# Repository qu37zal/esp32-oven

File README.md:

# esp32-oven
esp32-based temperature sensor/relay/wifi automation project to upcycle an inop "bradley" smoker

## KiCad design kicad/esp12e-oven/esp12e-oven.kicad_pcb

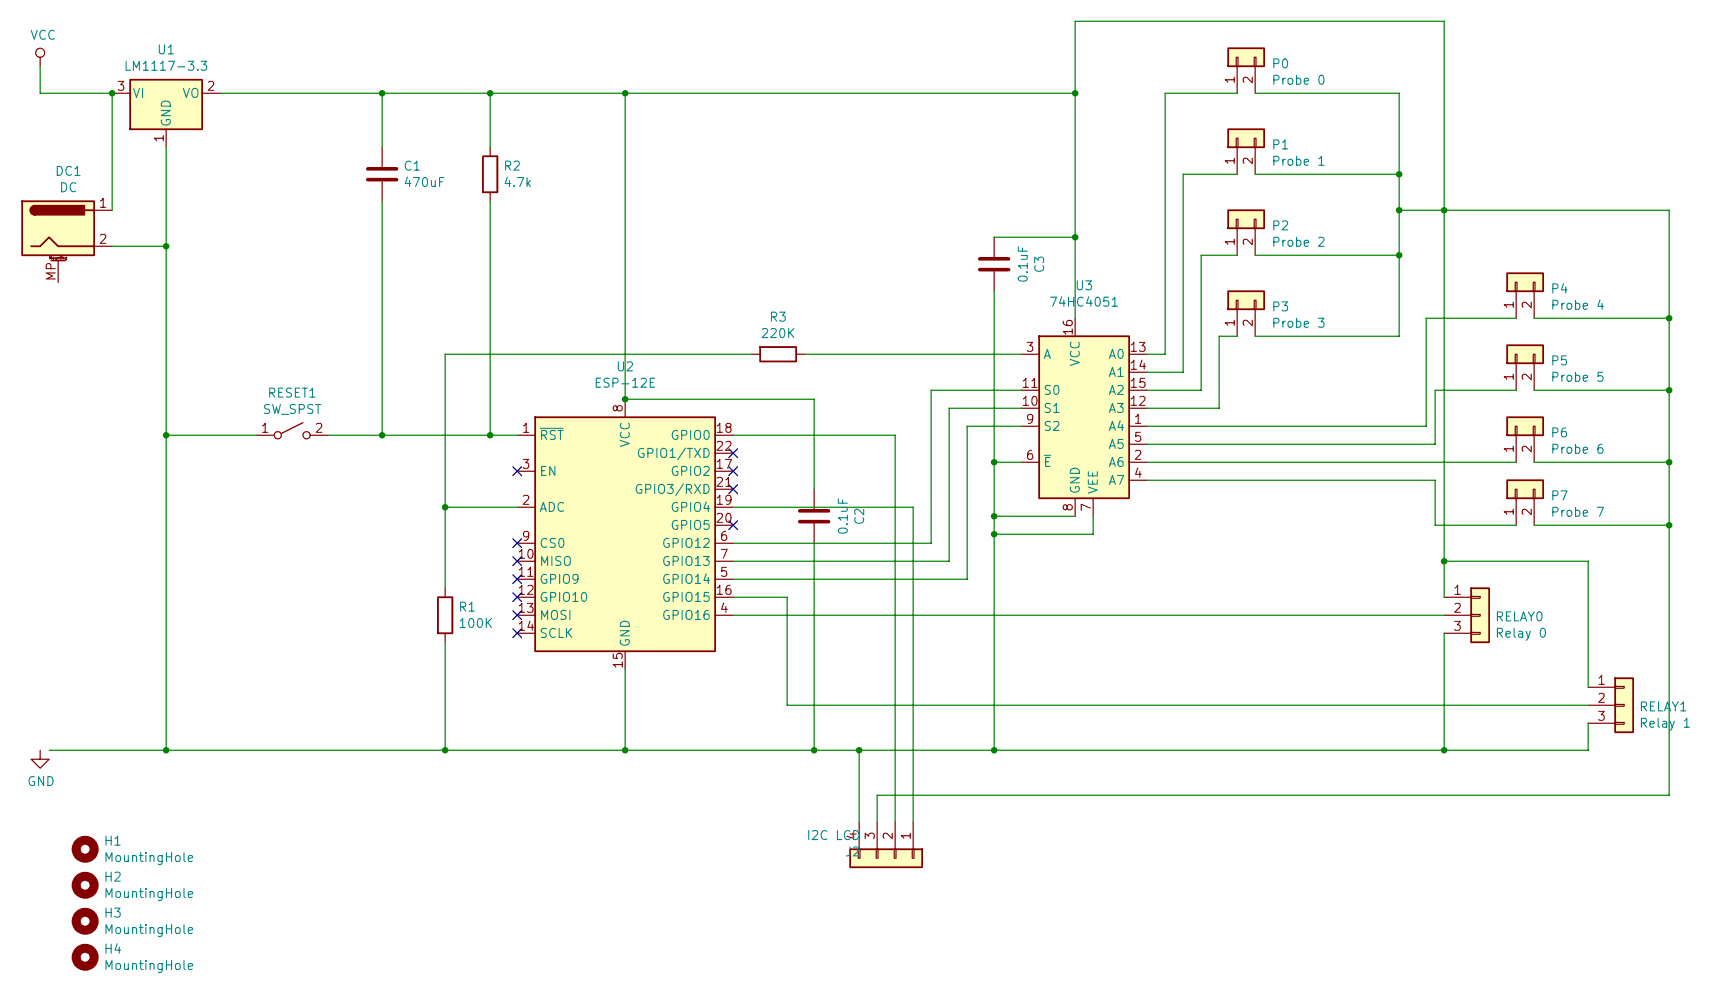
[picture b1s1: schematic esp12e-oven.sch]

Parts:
C1: 470uF; CP_Radial_D4.0mm_P1.50mm
C2, C3: 0.1uF; CP_Radial_D4.0mm_P1.50mm
DC1: DC; BarrelJack_Horizontal
H1, H2, H3, H4: MountingHole; MountingHole_2.5mm
J2: I2C LCD; PinHeader_1x04_P2.00mm_Vertical
P0: Probe 0; PinHeader_1x02_P2.00mm_Vertical
P1: Probe 1; PinHeader_1x02_P2.00mm_Vertical
P2: Probe 2; PinHeader_1x02_P2.00mm_Vertical
P3: Probe 3; PinHeader_1x02_P2.00mm_Vertical
P4: Probe 4; PinHeader_1x02_P2.00mm_Vertical
P5: Probe 5; PinHeader_1x02_P2.00mm_Vertical
P6: Probe 6; PinHeader_1x02_P2.00mm_Vertical
P7: Probe 7; PinHeader_1x02_P2.00mm_Vertical
R1: 100K; R_Axial_DIN0204_L3.6mm_D1.6mm_P5.08mm_Horizontal
R2: 4.7k; R_Axial_DIN0204_L3.6mm_D1.6mm_P5.08mm_Horizontal
R3: 220K; R_Axial_DIN0204_L3.6mm_D1.6mm_P5.08mm_Horizontal
RELAY0: Relay 0; PinSocket_1x03_P2.00mm_Horizontal
RELAY1: Relay 1; PinSocket_1x03_P2.00mm_Horizontal
RESET1: SW_SPST; KSA_Tactile_SPST
U1: LM1117-3.3; TO-220-3_Vertical
U2: ESP-12E
U3: 74HC4051; DIP-16_W7.62mm

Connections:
unnamed: C1.1, C2.2, C3.2, J2.3, P0.2, P1.2, P2.2, P3.2, P4.2, P5.2, P6.2, P7.2, R2.1, RELAY0.1, RELAY1.1, U1.2 (VO), U2.8 (VCC), U3.16 (VCC)
unnamed: C1.2, R2.2, RESET1.2 (B), U2.1 (~RST)
unnamed: C2.1, C3.1, DC1.2, J2.4, R1.2, RELAY0.3, RELAY1.3, RESET1.1 (A), U1.1 (GND), U2.15 (GND), U3.6 (~E), U3.7 (VEE), U3.8 (GND)
unnamed: J2.1, U2.19 (GPIO4)
unnamed: J2.2, U2.18 (GPIO0)
unnamed: P0.1, U3.13 (A0)
unnamed: P1.1, U3.14 (A1)
unnamed: P2.1, U3.15 (A2)
unnamed: P3.1, U3.12 (A3)
unnamed: P4.1, U3.1 (A4)
unnamed: P5.1, U3.5 (A5)
unnamed: P6.1, U3.2 (A6)
unnamed: P7.1, U3.4 (A7)
unnamed: R1.1, R3.2, U2.2 (ADC)
unnamed: R3.1, U3.3 (A)
unnamed: RELAY0.2, U2.4 (GPIO16)
unnamed: RELAY1.2, U2.16 (GPIO15)
unnamed: U2.5 (GPIO14), U3.9 (S2)
unnamed: U2.6 (GPIO12), U3.11 (S0)
unnamed: U2.7 (GPIO13), U3.10 (S1)
VCC: DC1.1, U1.3 (VI)

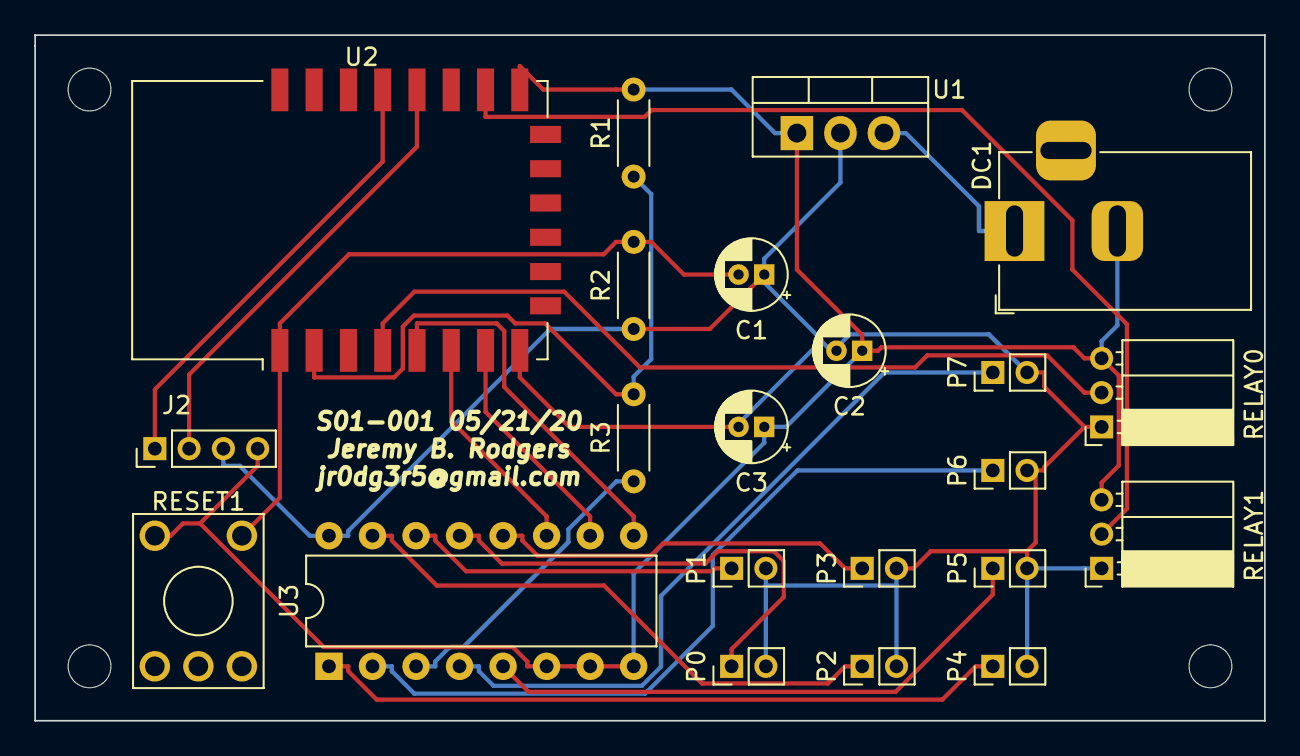
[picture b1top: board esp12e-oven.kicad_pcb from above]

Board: 2 copper layers, 71.8 x 40.0 mm, 26 parts (0 on the bottom side), 21 nets.

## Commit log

2020-05-20 Bump stringstream from 0.0.5 to 0.0.6 in /frontend
    Bumps [stringstream](https://github.com/mhart/StringStream) from 0.0.5 to 0.0.6.
    - [Release notes](https://github.com/mhart/StringStream/releases)
    - [Commits](https://github.com/mhart/StringStream/compare/v0.0.5...v0.0.6)
2020-05-20 Bump lodash.mergewith from 4.6.1 to 4.6.2 in /frontend
    Bumps [lodash.mergewith](https://github.com/lodash/lodash) from 4.6.1 to 4.6.2.
    - [Release notes](https://github.com/lodash/lodash/releases)
    - [Commits](https://github.com/lodash/lodash/commits)
2020-05-20 Bump js-yaml from 3.11.0 to 3.13.1 in /frontend
    Bumps [js-yaml](https://github.com/nodeca/js-yaml) from 3.11.0 to 3.13.1.
    - [Release notes](https://github.com/nodeca/js-yaml/releases)
    - [Changelog](https://github.com/nodeca/js-yaml/blob/master/CHANGELOG.md)
    - [Commits](https://github.com/nodeca/js-yaml/compare/3.11.0...3.13.1)
2020-05-20 Bump mixin-deep from 1.3.1 to 1.3.2 in /frontend
    Bumps [mixin-deep](https://github.com/jonschlinkert/mixin-deep) from 1.3.1 to 1.3.2.
    - [Release notes](https://github.com/jonschlinkert/mixin-deep/releases)
    - [Commits](https://github.com/jonschlinkert/mixin-deep/compare/1.3.1...1.3.2)
2020-05-20 added smoker arduino project
2020-05-20 added resource to maintain secrets (SSID etc)
2020-05-21 added kicad board layouts
2020-05-21 Revised boards
2020-05-21 moved arduino to firmware
2020-05-21 added backend and mongodb bindings
2020-05-21 added charting
2020-05-22 fixed async vue chart stuff
2020-05-22 graph updates
2020-05-26 some frontend work
2020-07-20 Bump lodash from 4.17.5 to 4.17.19 in /frontend
    Bumps [lodash](https://github.com/lodash/lodash) from 4.17.5 to 4.17.19.
    - [Release notes](https://github.com/lodash/lodash/releases)
    - [Commits](https://github.com/lodash/lodash/compare/4.17.5...4.17.19)
2020-07-20 Bump lodash from 4.17.15 to 4.17.19 in /backend
    Bumps [lodash](https://github.com/lodash/lodash) from 4.17.15 to 4.17.19.
    - [Release notes](https://github.com/lodash/lodash/releases)
    - [Commits](https://github.com/lodash/lodash/compare/4.17.15...4.17.19)
2020-09-03 Bump bl from 2.2.0 to 2.2.1 in /backend
    Bumps [bl](https://github.com/rvagg/bl) from 2.2.0 to 2.2.1.
    - [Release notes](https://github.com/rvagg/bl/releases)
    - [Commits](https://github.com/rvagg/bl/compare/v2.2.0...v2.2.1)
2020-12-04 Bump highlight.js from 9.15.9 to 9.18.5 in /frontend
    Bumps [highlight.js](https://github.com/highlightjs/highlight.js) from 9.15.9 to 9.18.5.
    - [Release notes](https://github.com/highlightjs/highlight.js/releases)
    - [Changelog](https://github.com/highlightjs/highlight.js/blob/9.18.5/CHANGES.md)
    - [Commits](https://github.com/highlightjs/highlight.js/compare/9.15.9...9.18.5)
2020-12-12 Bump ini from 1.3.5 to 1.3.8 in /frontend
    Bumps [ini](https://github.com/isaacs/ini) from 1.3.5 to 1.3.8.
    - [Release notes](https://github.com/isaacs/ini/releases)
    - [Commits](https://github.com/isaacs/ini/compare/v1.3.5...v1.3.8)
2020-12-12 Bump ini from 1.3.5 to 1.3.8 in /backend
    Bumps [ini](https://github.com/isaacs/ini) from 1.3.5 to 1.3.8.
    - [Release notes](https://github.com/isaacs/ini/releases)
    - [Commits](https://github.com/isaacs/ini/compare/v1.3.5...v1.3.8)
2021-01-06 Bump axios from 0.19.2 to 0.21.1 in /frontend
    Bumps [axios](https://github.com/axios/axios) from 0.19.2 to 0.21.1.
    - [Release notes](https://github.com/axios/axios/releases)
    - [Changelog](https://github.com/axios/axios/blob/v0.21.1/CHANGELOG.md)
    - [Commits](https://github.com/axios/axios/compare/v0.19.2...v0.21.1)
2021-03-10 Bump elliptic from 6.4.0 to 6.5.4 in /frontend
    Bumps [elliptic](https://github.com/indutny/elliptic) from 6.4.0 to 6.5.4.
    - [Release notes](https://github.com/indutny/elliptic/releases)
    - [Commits](https://github.com/indutny/elliptic/compare/v6.4.0...v6.5.4)
2021-03-31 Bump y18n from 3.2.1 to 3.2.2 in /backend
    Bumps [y18n](https://github.com/yargs/y18n) from 3.2.1 to 3.2.2.
    - [Release notes](https://github.com/yargs/y18n/releases)
    - [Changelog](https://github.com/yargs/y18n/blob/master/CHANGELOG.md)
    - [Commits](https://github.com/yargs/y18n/commits)
2021-04-01 Bump y18n from 3.2.1 to 3.2.2 in /frontend
    Bumps [y18n](https://github.com/yargs/y18n) from 3.2.1 to 3.2.2.
    - [Release notes](https://github.com/yargs/y18n/releases)
    - [Changelog](https://github.com/yargs/y18n/blob/master/CHANGELOG.md)
    - [Commits](https://github.com/yargs/y18n/commits)
2021-05-09 Bump url-parse from 1.4.7 to 1.5.1 in /frontend
    Bumps [url-parse](https://github.com/unshiftio/url-parse) from 1.4.7 to 1.5.1.
    - [Release notes](https://github.com/unshiftio/url-parse/releases)
    - [Commits](https://github.com/unshiftio/url-parse/compare/1.4.7...1.5.1)
2021-05-11 Bump lodash from 4.17.5 to 4.17.21 in /frontend
    Bumps [lodash](https://github.com/lodash/lodash) from 4.17.5 to 4.17.21.
    - [Release notes](https://github.com/lodash/lodash/releases)
    - [Commits](https://github.com/lodash/lodash/compare/4.17.5...4.17.21)
2021-05-11 Bump lodash from 4.17.15 to 4.17.21 in /backend
    Bumps [lodash](https://github.com/lodash/lodash) from 4.17.15 to 4.17.21.
    - [Release notes](https://github.com/lodash/lodash/releases)
    - [Commits](https://github.com/lodash/lodash/compare/4.17.15...4.17.21)
2021-05-11 Bump hosted-git-info from 2.6.0 to 2.8.9 in /frontend
    Bumps [hosted-git-info](https://github.com/npm/hosted-git-info) from 2.6.0 to 2.8.9.
    - [Release notes](https://github.com/npm/hosted-git-info/releases)
    - [Changelog](https://github.com/npm/hosted-git-info/blob/v2.8.9/CHANGELOG.md)
    - [Commits](https://github.com/npm/hosted-git-info/compare/v2.6.0...v2.8.9)
2021-05-26 Bump browserslist from 4.6.6 to 4.16.6 in /frontend
    Bumps [browserslist](https://github.com/browserslist/browserslist) from 4.6.6 to 4.16.6.
    - [Release notes](https://github.com/browserslist/browserslist/releases)
    - [Changelog](https://github.com/browserslist/browserslist/blob/main/CHANGELOG.md)
    - [Commits](https://github.com/browserslist/browserslist/compare/4.6.6...4.16.6)
2021-05-28 Bump dns-packet from 1.3.1 to 1.3.4 in /frontend
    Bumps [dns-packet](https://github.com/mafintosh/dns-packet) from 1.3.1 to 1.3.4.
    - [Release notes](https://github.com/mafintosh/dns-packet/releases)
    - [Changelog](https://github.com/mafintosh/dns-packet/blob/master/CHANGELOG.md)
    - [Commits](https://github.com/mafintosh/dns-packet/compare/v1.3.1...v1.3.4)
2021-08-04 Bump tar from 2.2.1 to 2.2.2 in /frontend
    Bumps [tar](https://github.com/npm/node-tar) from 2.2.1 to 2.2.2.
    - [Release notes](https://github.com/npm/node-tar/releases)
    - [Changelog](https://github.com/npm/node-tar/blob/main/CHANGELOG.md)
    - [Commits](https://github.com/npm/node-tar/compare/v2.2.1...v2.2.2)
    ---
    updated-dependencies:
2021-08-12 Bump path-parse from 1.0.5 to 1.0.7 in /frontend
    Bumps [path-parse](https://github.com/jbgutierrez/path-parse) from 1.0.5 to 1.0.7.
    - [Release notes](https://github.com/jbgutierrez/path-parse/releases)
    - [Commits](https://github.com/jbgutierrez/path-parse/commits/v1.0.7)
    ---
    updated-dependencies:
    - dependency-name: path-parse
2021-10-06 Bump url-parse from 1.4.7 to 1.5.3 in /frontend
    Bumps [url-parse](https://github.com/unshiftio/url-parse) from 1.4.7 to 1.5.3.
    - [Release notes](https://github.com/unshiftio/url-parse/releases)
    - [Commits](https://github.com/unshiftio/url-parse/compare/1.4.7...1.5.3)
    ---
    updated-dependencies:
    - dependency-name: url-parse
2022-02-19 Bump url-parse from 1.4.7 to 1.5.7 in /frontend
    Bumps [url-parse](https://github.com/unshiftio/url-parse) from 1.4.7 to 1.5.7.
    - [Release notes](https://github.com/unshiftio/url-parse/releases)
    - [Commits](https://github.com/unshiftio/url-parse/compare/1.4.7...1.5.7)
    ---
    updated-dependencies:
    - dependency-name: url-parse
2022-02-27 Bump url-parse from 1.4.7 to 1.5.10 in /frontend
    Bumps [url-parse](https://github.com/unshiftio/url-parse) from 1.4.7 to 1.5.10.
    - [Release notes](https://github.com/unshiftio/url-parse/releases)
    - [Commits](https://github.com/unshiftio/url-parse/compare/1.4.7...1.5.10)
    ---
    updated-dependencies:
    - dependency-name: url-parse
2022-06-01 Bump eventsource from 1.0.7 to 1.1.1 in /frontend
    Bumps [eventsource](https://github.com/EventSource/eventsource) from 1.0.7 to 1.1.1.
    - [Release notes](https://github.com/EventSource/eventsource/releases)
    - [Changelog](https://github.com/EventSource/eventsource/blob/master/HISTORY.md)
    - [Commits](https://github.com/EventSource/eventsource/compare/v1.0.7...v1.1.1)
    ---
    updated-dependencies:
2022-06-23 Bump shell-quote from 1.6.1 to 1.7.3 in /frontend
    Bumps [shell-quote](https://github.com/substack/node-shell-quote) from 1.6.1 to 1.7.3.
    - [Release notes](https://github.com/substack/node-shell-quote/releases)
    - [Changelog](https://github.com/substack/node-shell-quote/blob/master/CHANGELOG.md)
    - [Commits](https://github.com/substack/node-shell-quote/compare/1.6.1...1.7.3)
    ---
    updated-dependencies:
2022-11-17 Bump loader-utils and @vue/cli-service in /frontend
    Bumps [loader-utils](https://github.com/webpack/loader-utils) to 1.4.2 and updates ancestor dependency [@vue/cli-service](https://github.com/vuejs/vue-cli/tree/HEAD/packages/@vue/cli-service). These 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
    Updates `loader-utils` from 1.4.0 to 1.4.2
    - [Release notes](https://github.com/webpack/loader-utils/releases)
    - [Changelog](https://github.com/webpack/loader-utils/blob/v1.4.2/CHANGELOG.md)
    - [Commits](https://github.com/webpack/loader-utils/compare/v1.4.0...v1.4.2)
    Updates `@vue/cli-service` from 3.12.1 to 5.0.8
2022-12-06 Bump decode-uri-component from 0.2.0 to 0.2.2 in /frontend
    Bumps [decode-uri-component](https://github.com/SamVerschueren/decode-uri-component) from 0.2.0 to 0.2.2.
    - [Release notes](https://github.com/SamVerschueren/decode-uri-component/releases)
    - [Commits](https://github.com/SamVerschueren/decode-uri-component/compare/v0.2.0...v0.2.2)
    ---
    updated-dependencies:
    - dependency-name: decode-uri-component
2022-12-07 Bump qs, body-parser and express in /backend
    Bumps [qs](https://github.com/ljharb/qs) to 6.11.0 and updates ancestor dependencies [qs](https://github.com/ljharb/qs), [body-parser](https://github.com/expressjs/body-parser) and [express](https://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
    Updates `qs` from 6.7.0 to 6.11.0
    - [Release notes](https://github.com/ljharb/qs/releases)
    - [Changelog](https://github.com/ljharb/qs/blob/main/CHANGELOG.md)
    - [Commits](https://github.com/ljharb/qs/compare/v6.7.0...v6.11.0)
    Updates `body-parser` from 1.19.0 to 1.20.1
2022-12-12 Bump express from 4.17.1 to 4.17.3 in /backend
    Bumps [express](https://github.com/expressjs/express) from 4.17.1 to 4.17.3.
    - [Release notes](https://github.com/expressjs/express/releases)
    - [Changelog](https://github.com/expressjs/express/blob/master/History.md)
    - [Commits](https://github.com/expressjs/express/compare/4.17.1...4.17.3)
    ---
    updated-dependencies:
2023-01-04 Bump json5, @vue/cli-plugin-babel and @vue/cli-service in /frontend
    Bumps [json5](https://github.com/json5/json5) to 2.2.3 and updates ancestor dependencies [json5](https://github.com/json5/json5), [@vue/cli-plugin-babel](https://github.com/vuejs/vue-cli/tree/HEAD/pa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
    Updates `json5` from 1.0.1 to 2.2.3
    - [Release notes](https://github.com/json5/json5/releases)
    - [Changelog](https://github.com/json5/json5/blob/main/CHANGELOG.md)
    - [Commits](https://github.com/json5/json5/compare/v1.0.1...v2.2.3)
    Updates `@vue/cli-plugin-b
